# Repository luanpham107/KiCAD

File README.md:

# KiCAD
## 01SCHLib
- KiCAD pml
## 02FootprintLib
- KiCAD pml
## 03Document
- KiCAD pml
## 04
## 05Projects
### AutoTurnLightOn

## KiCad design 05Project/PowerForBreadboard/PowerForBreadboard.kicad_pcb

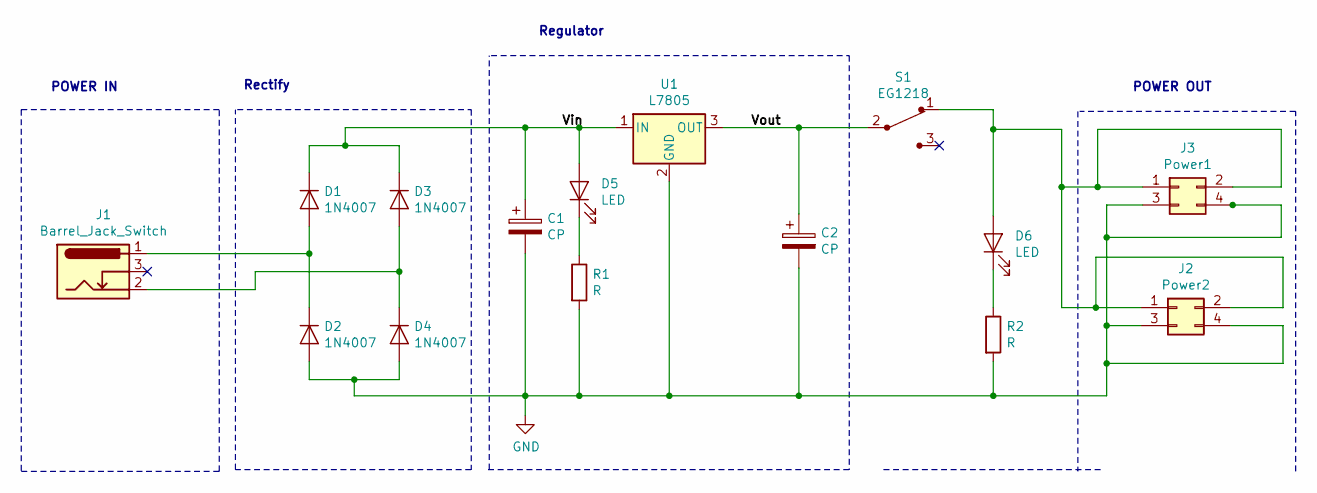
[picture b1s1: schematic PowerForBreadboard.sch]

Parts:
C1, C2: CP; CP_Radial_D6.3mm_P2.50mm
D1, D2, D3, D4: 1N4007; D_DO-41_SOD81_P10.16mm_Horizontal
D5, D6: LED; LED_D5.0mm
J1: Barrel_Jack_Switch; BarrelJack_Horizontal
J2: Power2; PinHeader_2x02_P2.54mm_Horizontal
J3: Power1; PinHeader_2x02_P2.54mm_Horizontal
R1, R2: R; R_Axial_DIN0207_L6.3mm_D2.5mm_P10.16mm_Horizontal
S1: EG1218; Switch_Slide_11.6x4mm_EG1218; MPN EG1218; Digi-Key_PN EG1903-ND
U1: L7805; TO-220-3_Vertical

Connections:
/Vin: C1.1, D1.1 (K), D3.1 (K), D5.2 (A), U1.1 (IN)
/Vout: C2.1, S1.2, U1.3 (OUT)
GND: C1.2, C2.2, D2.2 (A), D4.2 (A), J2.3, J2.4, J3.3, J3.4, R1.2, R2.2, U1.2 (GND)
unnamed: D1.2 (A), D2.1 (K), J1.1
unnamed: D3.2 (A), D4.1 (K), J1.2
unnamed: D5.1 (K), R1.1
unnamed: D6.1 (K), R2.1
unnamed: D6.2 (A), J2.1, J2.2, J3.1, J3.2, S1.1

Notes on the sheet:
POWER IN
Rectify
Regulator
POWER OUT

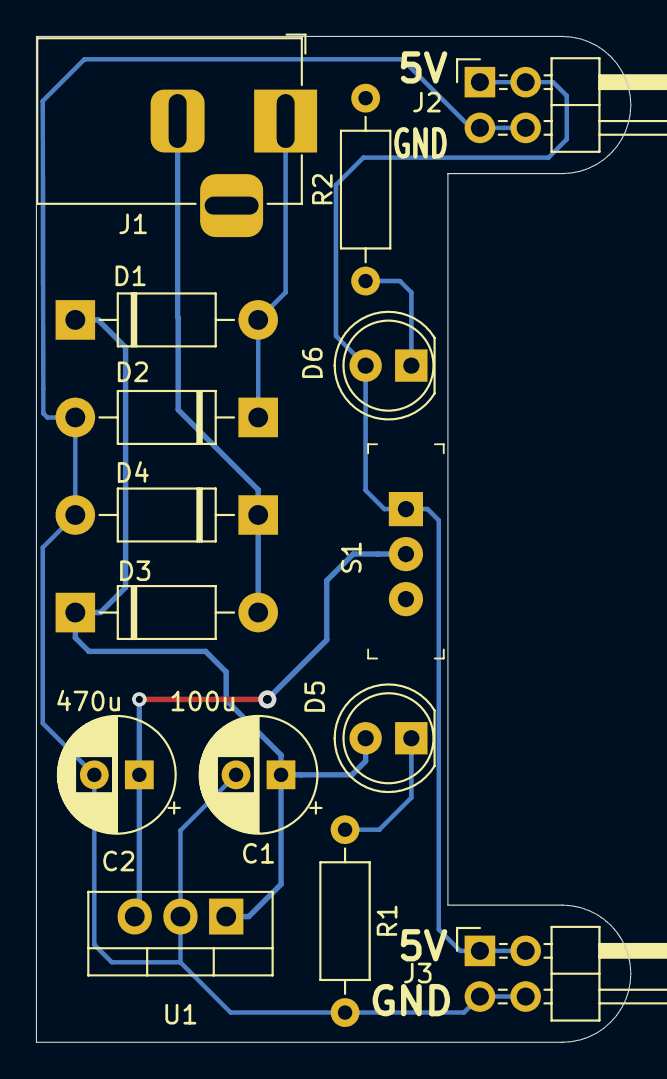
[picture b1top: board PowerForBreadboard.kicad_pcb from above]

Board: 2 copper layers, 33.0 x 55.9 mm, 15 parts (0 on the bottom side), 8 nets.

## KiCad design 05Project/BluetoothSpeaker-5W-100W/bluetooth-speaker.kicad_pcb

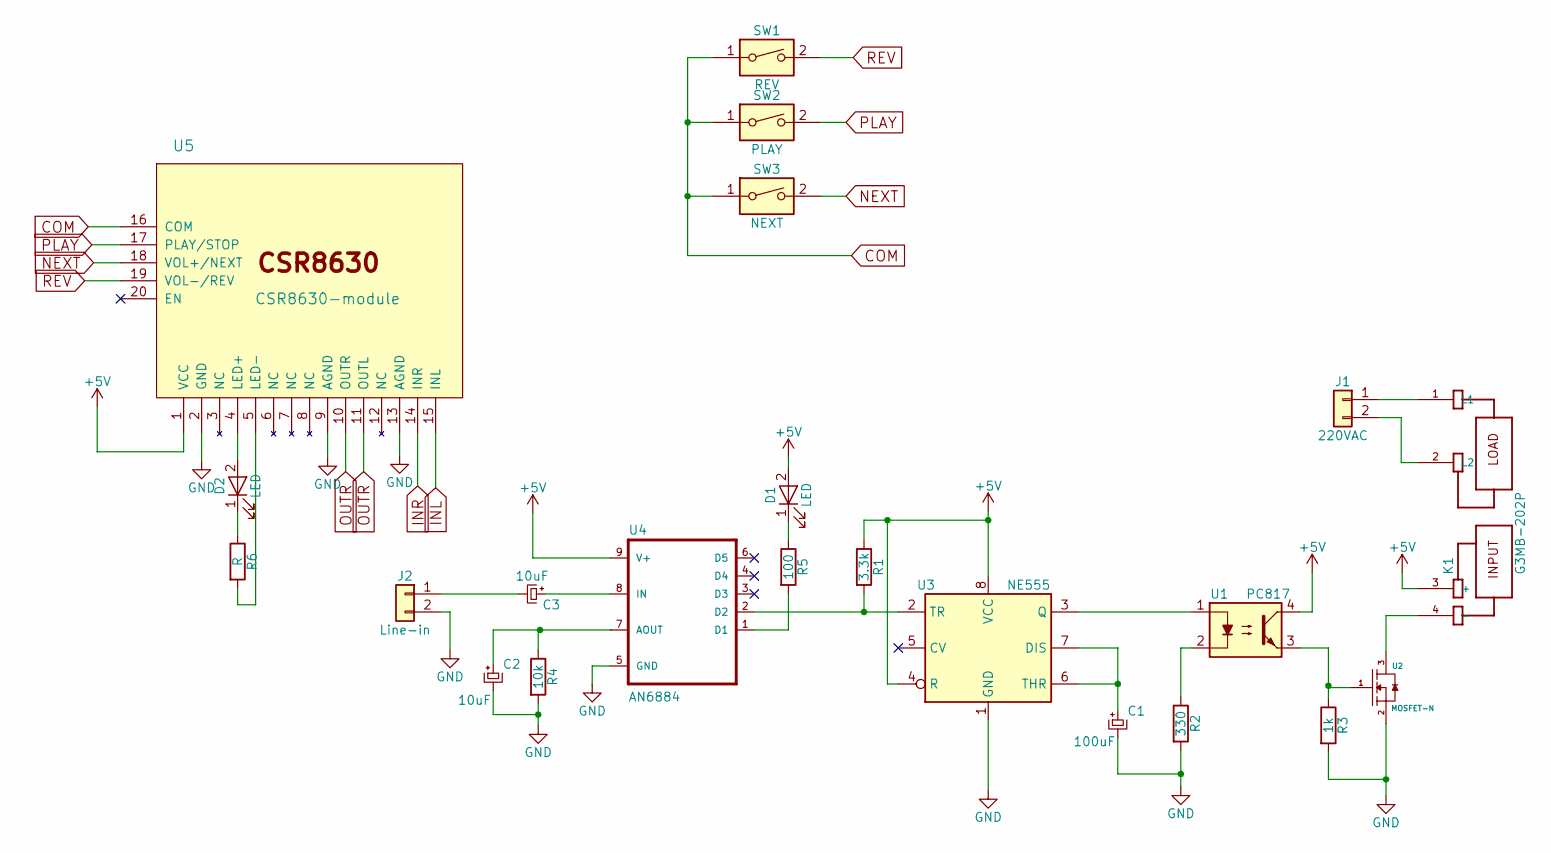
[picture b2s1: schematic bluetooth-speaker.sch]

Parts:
C1: 100uF; CP_Radial_D6.3mm_P2.50mm
C2, C3: 10uF; CP_Radial_D6.3mm_P2.50mm
D1, D2: LED; LED_D5.0mm_FlatTop
J1: 220VAC; TerminalBlock_Altech_AK300-2_P5.00mm
J2: Line-in; TerminalBlock_Altech_AK300-2_P5.00mm
K1: G3MB-202P; RELAY_G3MB-202P
R1: 3.3k; R_0805_HandSoldering
R2: 330; R_0805_HandSoldering
R3: 1k; R_0805_HandSoldering
R4: 10k; R_0805_HandSoldering
R5: 100; R_0805_HandSoldering
R6: R; R_0805_HandSoldering
SW1: REV; SW_Tactile_Straight_KSA0Axx1LFTR
SW2: PLAY; SW_Tactile_Straight_KSA0Axx1LFTR
SW3: NEXT; SW_Tactile_Straight_KSA0Axx1LFTR
U1: PC817; DIP-4_W7.62mm
U2: MOSFET-N; TO-220-3_Vertical
U3: NE555; DIP254P762X533-8
U4: AN6884; SIP9
U5: CSR8630-module

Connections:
+5V: D1.2 (A), K1.3 (+), R1.1, U1.4, U3.4 (R), U3.8 (VCC), U4.9 (V+), U5.1 (VCC)
COM: SW1.1, SW2.1, SW3.1, U5.16 (COM)
INL: U5.15 (INL)
INR: U5.14 (INR)
NEXT: SW3.2, U5.18 (VOL+/NEXT)
unnamed: C1.1, U3.6 (THR), U3.7 (DIS)
unnamed: C3.1, U4.8 (IN)
unnamed: C3.2, J2.1
unnamed: D1.1 (K), R5.1
unnamed: D2.1 (K), R6.1
unnamed: D2.2 (A), U5.4 (LED+)
unnamed: J1.1, K1.1 (L1)
unnamed: J1.2, K1.2 (L2)
unnamed: K1.4 (-), U2.3
unnamed: R1.2, U3.2 (TR), U4.2 (D2)
unnamed: R2.1, U1.2
unnamed: R3.1, U1.3, U2.1
unnamed: R5.2, U4.1 (D1)
unnamed: R6.2, U5.5 (LED-)
unnamed: U1.1, U3.3 (Q)
OUTR: U5.10 (OUTR), U5.11 (OUTL)
PLAY: SW2.2, U5.17 (PLAY/STOP)
REV: SW1.2, U5.19 (VOL-/REV)

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
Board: 2 copper layers, 22 parts (0 on the bottom side), 22 nets, no tracks yet.

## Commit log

2017-12-05 First init
2017-12-05 fix space
2017-12-06 Add project
2017-12-06 Schematic bluetooth Speaker
2017-12-09 Add footprint done halt
2017-12-09 first innit
2018-08-03 Update ngocluanpham lib
2019-11-08 Power for breadboard
2019-11-08 Fix cooper fill
2019-11-08 Update rounded corner
2019-11-11 project 3 course
